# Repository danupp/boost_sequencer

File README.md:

# boost_sequencer
Universal sequencer for radio applications with 12 to 28V boost regulator for coaxial relays. More info at: sm6vfz.wordpress.com

---
Changelog/notes:

-Ta bort lödpasta från TPs.\
-Schottky: SS16_R1_00001\
-PMOS: SI2347DS-T1-GE3\
-NMOS: SI2318DS-T1-BE3\
-2k2->3k0

Löd alltid relä vid test.

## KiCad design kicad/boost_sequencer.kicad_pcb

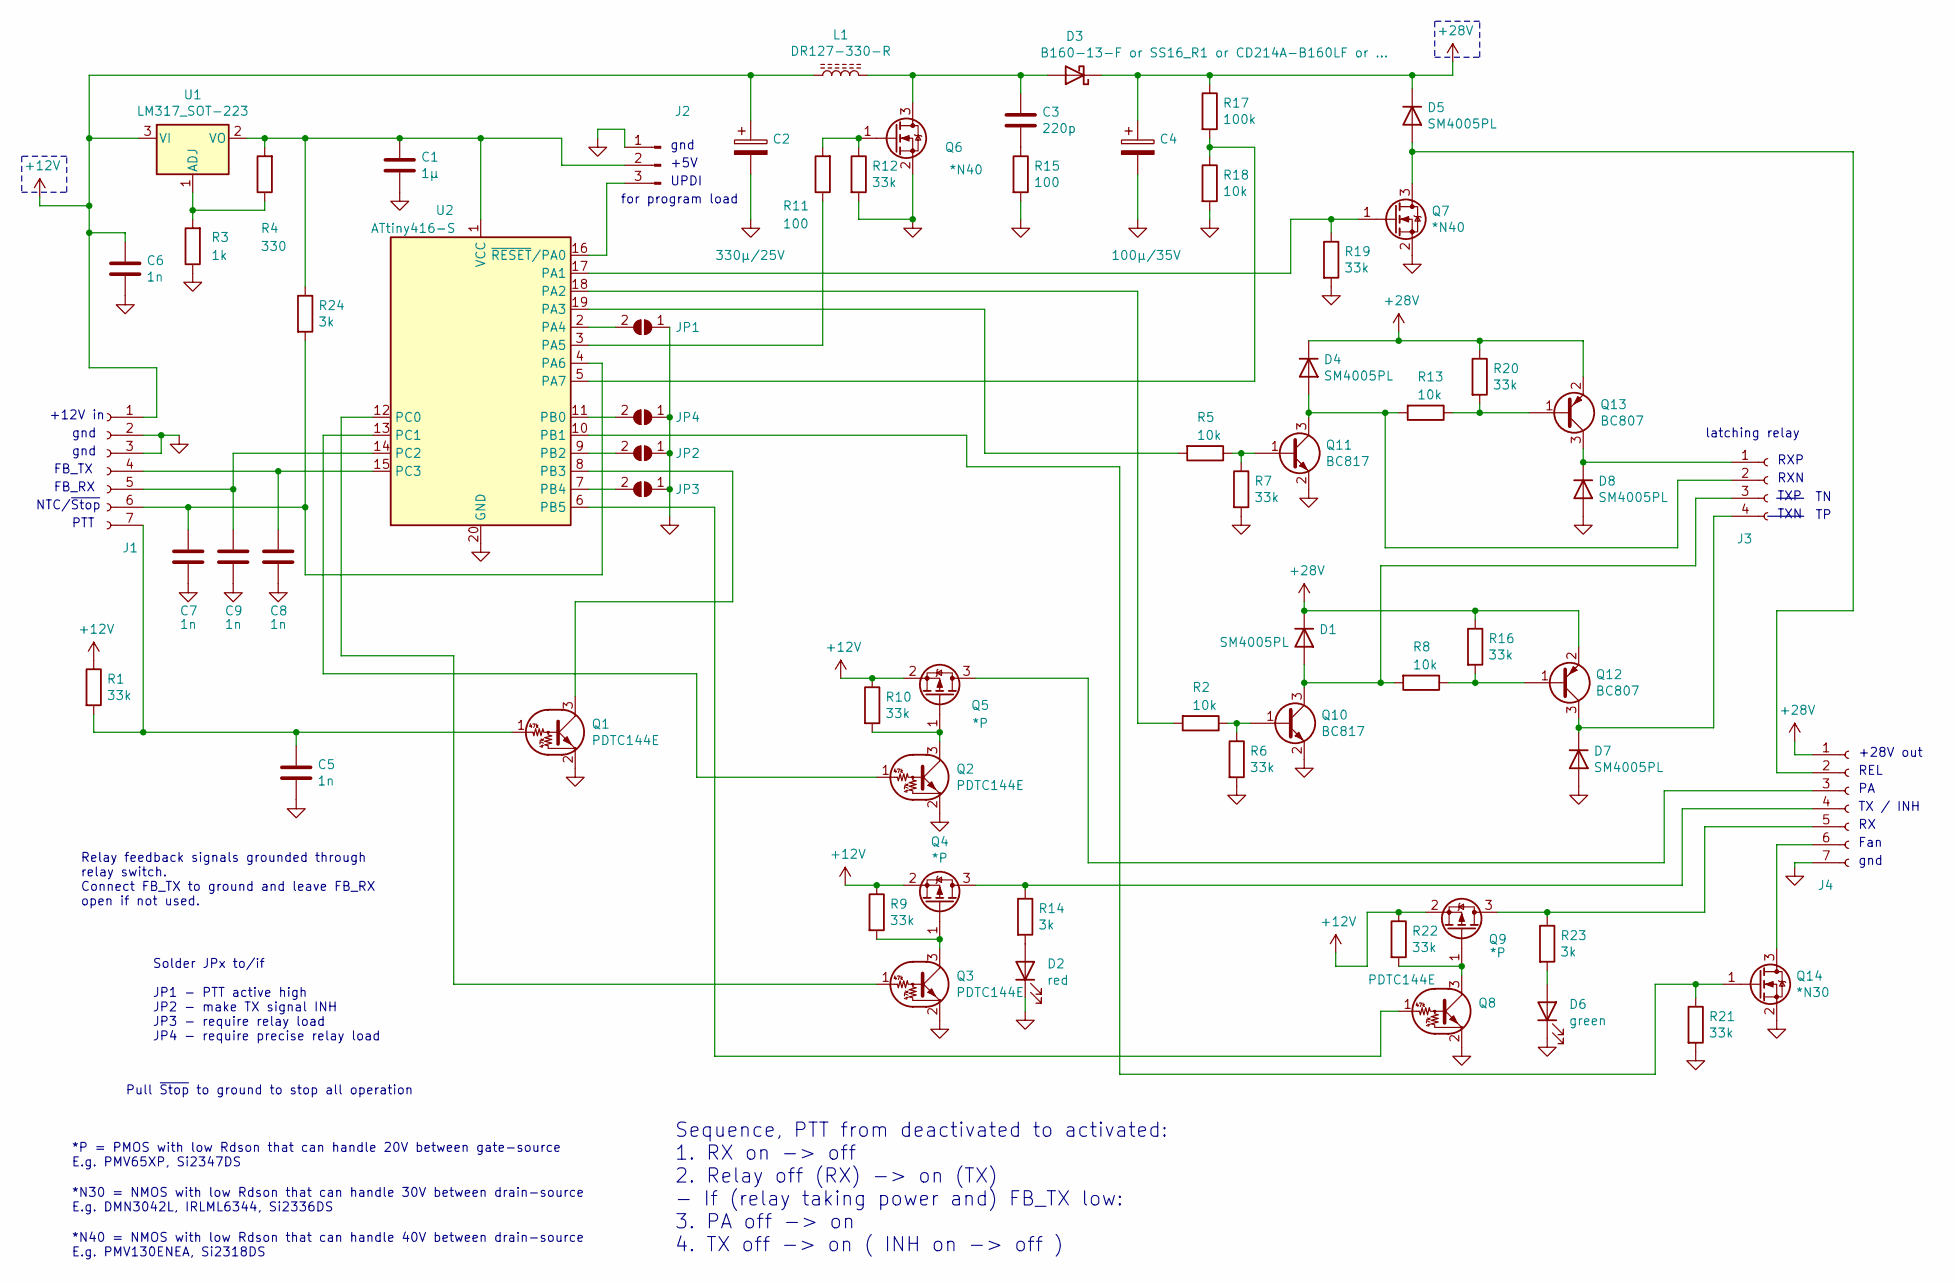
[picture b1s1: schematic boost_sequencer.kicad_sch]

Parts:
C1: 1µ; C_0603_1608Metric
C2: 330µ/25V; CP_Radial_D8.0mm_P3.50mm
C3: 220p; C_0603_1608Metric
C4: 100µ/35V; CP_Radial_D6.3mm_P2.50mm
C5, C6, C7, C8, C9: 1n; C_0603_1608Metric
D1, D4, D5, D7, D8: SM4005PL; D_SOD-123F
D2: red; LED_0603_1608Metric
D3: B160-13-F or SS16_R1 or CD214A-B160LF or ...; D_SMA
D6: green; LED_0603_1608Metric
J1, J4: Conn_01x07_Female; PinHeader_1x07_P2.54mm_Vertical
J2: Conn_01x03_Male; PinHeader_1x03_P2.54mm_Vertical
J3: Conn_01x04_Female; PinHeader_1x04_P2.54mm_Vertical
JP1, JP2, JP3, JP4: SolderJumper_2_Open; SolderJumper-2_P1.3mm_Open_RoundedPad1.0x1.5mm
L1: DR127-330-R; L_12x12mm_H8mm
Q1, Q2, Q3, Q8: PDTC144E; SOT-323_SC-70
Q4, Q5, Q9: *P; SOT-23
Q6, Q7: *N40; SOT-23
Q10, Q11: BC817; SOT-23
Q12, Q13: BC807; SOT-23
Q14: *N30; SOT-23
R1, R6, R7, R9, R10, R12, R16, R19, R20, R21, R22: 33k; R_0603_1608Metric
R2, R5, R8, R13, R18: 10k; R_0603_1608Metric
R3: 1k; R_0603_1608Metric
R4: 330; R_0603_1608Metric
R11, R15: 100; R_0603_1608Metric
R14, R23, R24: 3k; R_0603_1608Metric
R17: 100k; R_0603_1608Metric
U1: LM317_SOT-223; SOT-223-3_TabPin2
U2: ATtiny416-S; SOIC-20W_7.5x12.8mm_P1.27mm

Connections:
+12V: C2.1, C6.1, J1.1, L1.1, Q4.2 (S), Q5.2 (S), Q9.2 (S), R1.1, R9.1, R10.1, R22.1, U1.3 (VI)
+28V: C4.1, D1.1 (K), D3.1 (K), D4.1 (K), D5.1 (K), J4.1, Q12.2 (E), Q13.2 (E), R16.1, R17.1, R20.1
GND: C1.2, C2.2, C4.2, C5.2, C6.2, C7.2, C8.2, C9.2, D2.1 (K), D6.1 (K), D7.2 (A), D8.2 (A), J1.2, J1.3, J2.1, J4.7, JP1.1 (A), JP2.1 (A), JP3.1 (A), JP4.1 (A), Q1.2 (E), Q2.2 (E), Q3.2 (E), Q6.2 (S), Q7.2 (S), Q8.2 (E), Q10.2 (E), Q11.2 (E), Q14.2 (S), R3.1, R6.2, R7.2, R12.2, R15.2, R18.2, R19.2, R21.2, U2.20 (GND)
unnamed: C1.1, J2.2, R4.2, R24.1, U1.2 (VO), U2.1 (VCC)
unnamed: C3.1, D3.2 (A), L1.2, Q6.3 (D)
unnamed: C3.2, R15.1
unnamed: C5.1, J1.7, Q1.1 (B), R1.2
unnamed: C7.1, J1.6, R24.2, U2.4 (PA6)
unnamed: C8.1, J1.4, U2.15 (PC3)
unnamed: C9.1, J1.5, U2.14 (PC2)
unnamed: D1.2 (A), J3.3, Q10.3 (C), R8.2
unnamed: D2.2 (A), R14.2
unnamed: D4.2 (A), J3.2, Q11.3 (C), R13.2
unnamed: D5.2 (A), J4.2, Q7.3 (D)
unnamed: D6.2 (A), R23.2
unnamed: D7.1 (K), J3.4, Q12.3 (C)
unnamed: D8.1 (K), J3.1, Q13.3 (C)
unnamed: J2.3, U2.16 (~RESET/PA0)
unnamed: J4.3, Q5.3 (D)
unnamed: J4.4, Q4.3 (D), R14.1
unnamed: J4.5, Q9.3 (D), R23.1
unnamed: J4.6, Q14.3 (D)
unnamed: JP1.2 (B), U2.2 (PA4)
unnamed: JP2.2 (B), U2.9 (PB2)
unnamed: JP3.2 (B), U2.7 (PB4)
unnamed: JP4.2 (B), U2.11 (PB0)
unnamed: Q1.3 (C), U2.8 (PB3)
unnamed: Q2.1 (B), U2.13 (PC1)
unnamed: Q2.3 (C), Q5.1 (G), R10.2
unnamed: Q3.1 (B), U2.12 (PC0)
unnamed: Q3.3 (C), Q4.1 (G), R9.2
unnamed: Q6.1 (G), R11.2, R12.1
unnamed: Q7.1 (G), R19.1, U2.17 (PA1)
unnamed: Q8.1 (B), U2.6 (PB5)
unnamed: Q8.3 (C), Q9.1 (G), R22.2
unnamed: Q10.1 (B), R2.1, R6.1
unnamed: Q11.1 (B), R5.1, R7.1
unnamed: Q12.1 (B), R8.1, R16.2
unnamed: Q13.1 (B), R13.1, R20.2
unnamed: Q14.1 (G), R21.1, U2.10 (PB1)
unnamed: R2.2, U2.18 (PA2)
unnamed: R3.2, R4.1, U1.1 (ADJ)
unnamed: R5.2, U2.19 (PA3)
unnamed: R11.1, U2.3 (PA5)
unnamed: R17.2, R18.1, U2.5 (PA7)

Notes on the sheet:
TX / INH
*N40 = NMOS with low Rdson that can handle 40V between drain-source E.g. PMV130ENEA, Si2318DS
+12V in
RXN
TXP
NTC/~{Stop}
+28V out
PTT
gnd
RXP
latching relay
Fan
Relay feedback signals grounded through relay switch. Connect FB_TX to ground and leave FB_RX open if not used.
UPDI
Solder JPx to/if JP1 - PTT active high JP2 - make TX signal INH JP3 - require relay load JP4 - require precise relay load
*P = PMOS with low Rdson that can handle 20V between gate-source E.g. PMV65XP, Si2347DS
+5V
Pull ~{Stop} to ground to stop all operation
for program load
Sequence, PTT from deactivated to activated: 1. RX on -> off 2. Relay off (RX) -> on (TX) - If (relay taking power and) FB_TX low: 3. PA off -> on 4. TX off -> on ( INH on -> off )
FB_TX
TXN
*N30 = NMOS with low Rdson that can handle 30V between drain-source E.g. DMN3042L, IRLML6344, Si2336DS
REL
FB_RX

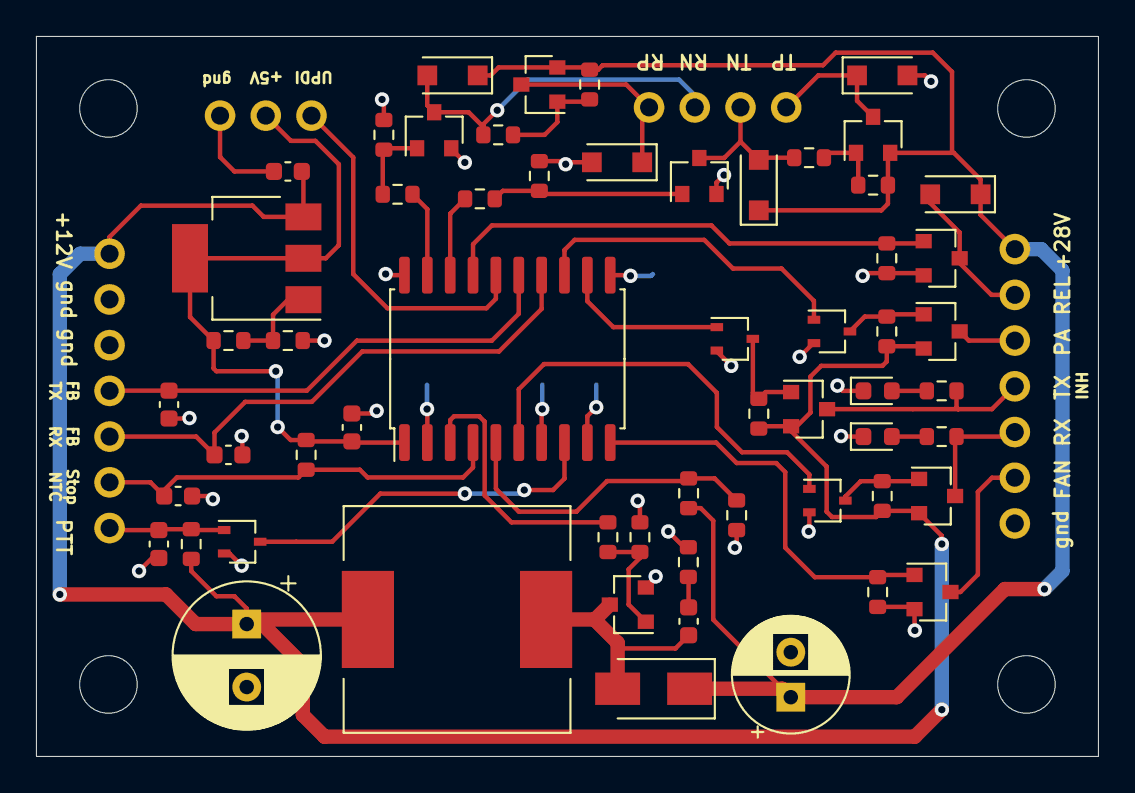
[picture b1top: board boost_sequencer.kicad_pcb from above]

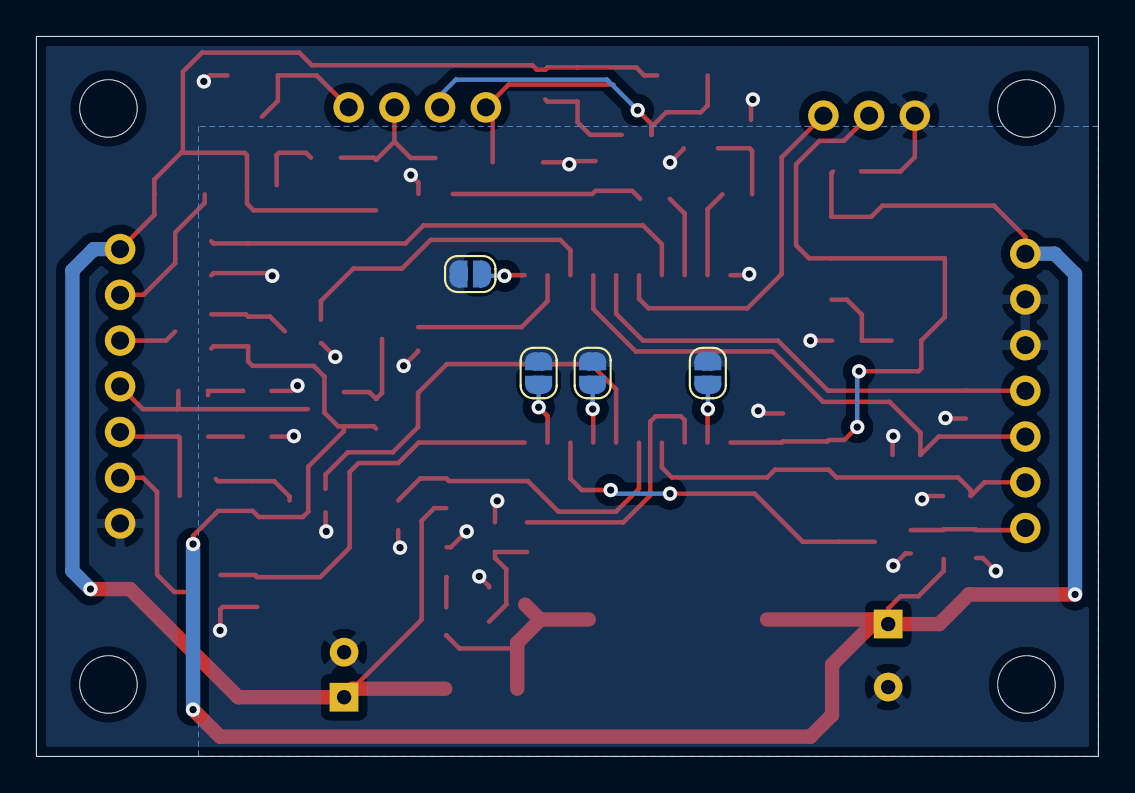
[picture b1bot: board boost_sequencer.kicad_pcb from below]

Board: 2 copper layers, 59.0 x 40.0 mm, 66 parts (4 on the bottom side), 45 nets.

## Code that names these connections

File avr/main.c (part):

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//#include <string.h>
#endif

#define PTT PIN3_bm // PB3
#define PA PIN1_bm // PC1
#define TX_INH PIN0_bm // PC0
#define RX PIN5_bm // PB5
#define RELAY PIN1_bm // PA1
#define REL_L_TX PIN2_bm // PA2
#define REL_L_RX PIN3_bm // PA3
#define BUCK_GATE PIN5_bm // PA5
#define STOP_NTC PIN6_bm // PA6
#define BUCK_FB PIN7_bm // PA7 
#define REL_FB_TX PIN3_bm // PC3
#define REL_FB_RX PIN2_bm // PC2
#define FAN PIN1_bm // PB1
#define JP1 PIN4_bm // PA4    -- PTT active high
#define JP2 PIN2_bm // PB2    -- TX / INH
#define JP3 PIN4_bm // PB4    -- Require relay load
#define JP4 PIN0_bm // PB0    -- Precise relay load monitoring
#ifdef DEBUG
#define TXD PIN2_bm // PB2    -- debug only
#endif

#define LOADPOINT_EEADDR (int*) 0
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  int loadpoint, load_l, load_h;
  
  PORTA.DIR = REL_L_RX | REL_L_TX | RELAY | BUCK_GATE; // outputs
  PORTA.PIN6CTRL = 0x04; // digital input disable for AIN6/PA6
  PORTA.PIN7CTRL = 0x04; // digital input disable for AINP0/AIN7/PA7
  PORTA.OUT = 0x00;
  PORTA.PIN4CTRL = 0x08; // enable pull-up for JP1
  PORTB.DIR = RX | FAN;
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  
  EVSYS.SYNCCH0 = 0x02; // TCA0_OVF
  EVSYS.ASYNCCH0 = 0x01; // CCL_LUT0
  //EVSYS.ASYNCUSER8 = 0x01; // SYNCCH0 -> EVOUT0/PA2 to see max switch freq 
  EVSYS.ASYNCUSER2 = 0x01; // SYNCCH0 -> LUT0
  EVSYS.ASYNCUSER0 = 0x03; // ASYNCCH0 -> TCB0
  
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
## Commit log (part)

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2021-08-18 First complete commit
2021-11-18 Fixed details in code. Added Gerber files.
2022-01-09 Removed non-relevant setfuse.sh
2022-01-14 Relay activates instantly. And updated schematic.
2022-01-19 New schematic pdf.
2022-02-02 ubc ver 1
2022-02-26 10ms added
2022-08-10 Intermediate commit.
2022-08-27 Reduced blind time if PTT re-activation when going from TX to RX
2023-09-21 first on new board
2023-11-06 PCB ordered
2023-12-21 new pdf schematic plot
2025-10-28 seems ok
